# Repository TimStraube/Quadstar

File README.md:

# Thetafly

## Description

Thetafly is a project which includes python classes for simulating a quadcopter system. The simulation software is in a prototype stage with a lot of bugs still to be fixed and furture deep testing required.
With the help of the functionality a quadcopter prototyp has beeing build, mainly for fun and research purposes. The hardware is mostly finished but a lot of firmware still has to be written before flight testing can begin.

## Architecture

## Simulation

### Configuration

Make sure you setup a pyenv with the libs defined in pyproject.toml:

```pyenv activate thetafly```

Post activation of the pyenv you can simply run the simulator with a bash script:

```bash start.sh```

## Delopyment

### Joystick

To sample joystick values and send them to the main flight computer run:

```PYTHONPATH=src poetry run python -m util.joystick```.

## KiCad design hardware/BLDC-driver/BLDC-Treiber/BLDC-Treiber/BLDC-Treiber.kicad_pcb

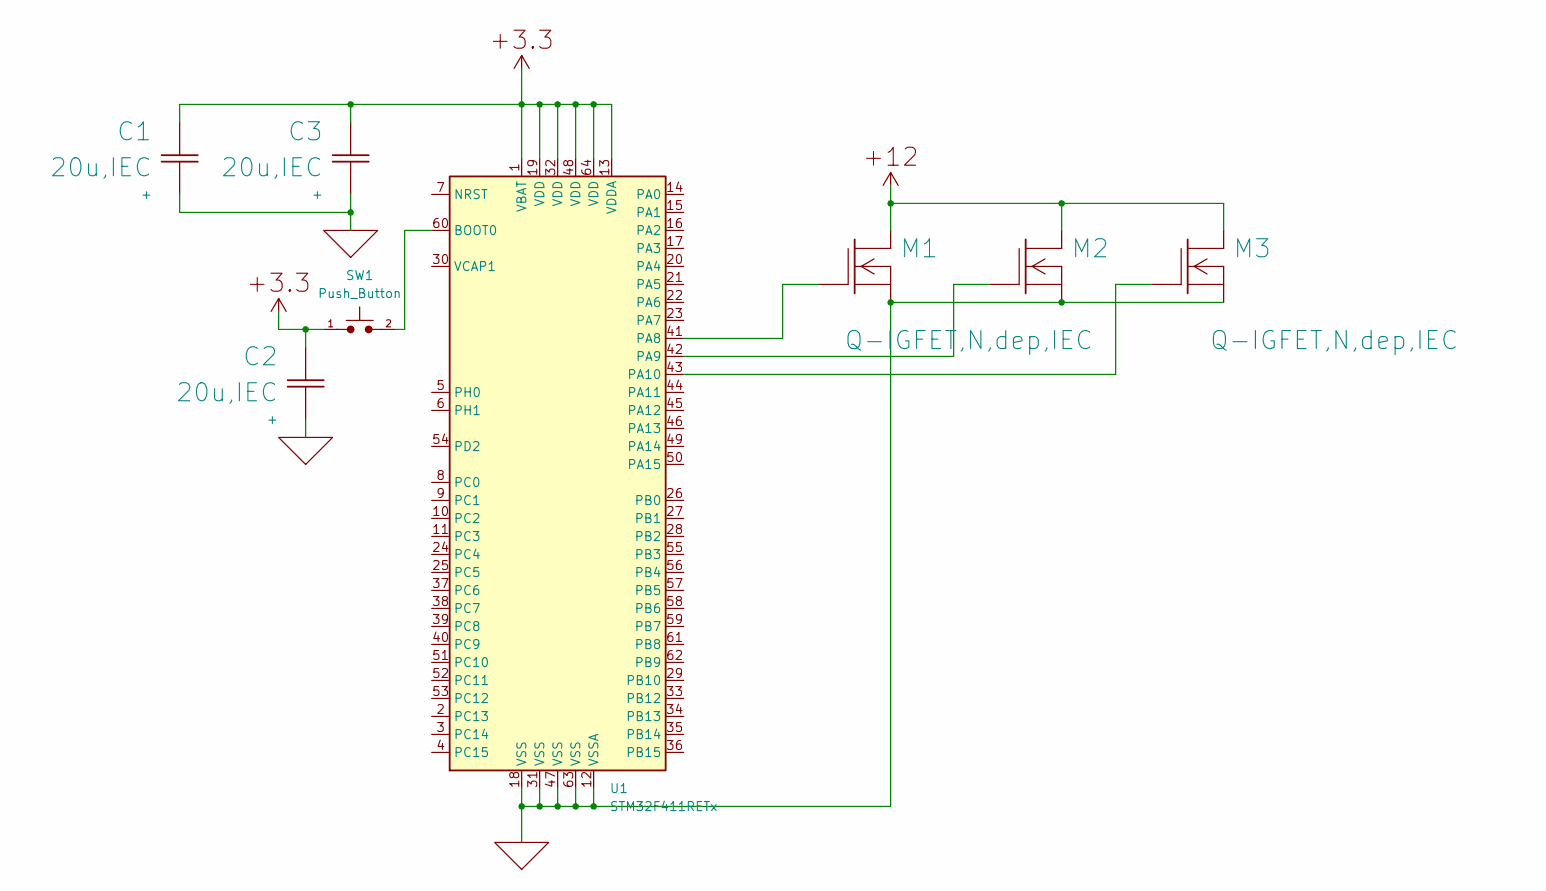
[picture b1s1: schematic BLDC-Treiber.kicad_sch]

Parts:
C1, C3: 20u,IEC; CP_Elec_8x5.4
C2: 20u,IEC; CP_Elec_3x5.3
M1, M2, M3: Q-IGFET,N,dep,IEC; DirectFET_SB
SW1: Push_Button; SW_PUSH_6mm
U1: STM32F411RETx; LQFP-64_10x10mm_P0.5mm

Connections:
unnamed: M1.2 (G), U1.41 (PA8)
unnamed: M2.2 (G), U1.42 (PA9)
unnamed: M3.2 (G), U1.43 (PA10)
unnamed: SW1.2, U1.60 (BOOT0)
P,+3.3: C1.1 (+), C2.1 (+), C3.1 (+), SW1.1, U1.1 (VBAT), U1.13 (VDDA), U1.19 (VDD), U1.32 (VDD), U1.48 (VDD), U1.64 (VDD)
P,+12: M1.1 (D), M2.1 (D), M3.1 (D)
P,GND: C1.2 (-), C2.2 (-), C3.2 (-), M1.3 (S), M2.3 (S), M3.3 (S), U1.12 (VSSA), U1.18 (VSS), U1.31 (VSS), U1.47 (VSS), U1.63 (VSS)

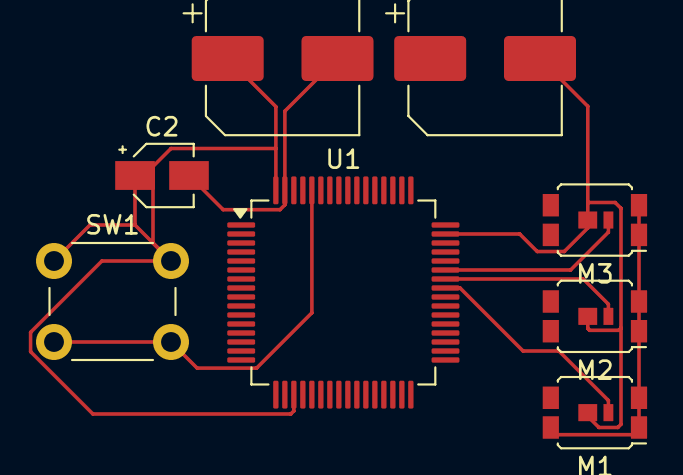
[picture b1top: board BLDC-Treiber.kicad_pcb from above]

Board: 2 copper layers, 8 parts (0 on the bottom side), 7 nets.

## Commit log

2024-09-27 Transfer from codeberg
2024-09-27 Remove unused images
2024-09-27 Cleanup
2024-09-27 Bug fixes
2024-09-27 Added quadsoft which includes the program for the onboard pid-controller
2024-09-28 Fixed bugs
2024-09-28 Changed language of README.md to english
2024-09-29 Updated LICENSE
2024-10-01 Started translation to english
2024-10-01 Translated variables and fixed bug in the report
2024-10-01 Added .gitignore
2024-10-01 Fixed images reference
2024-10-03 Removed temporary statements
2024-10-03 Bug fixes in the report
2024-10-04 Updated info and language
2024-10-05 Translated programs and fixed report
2024-10-06 Mores translations
2024-10-06 Fixed quadcopter dynamics model
2024-10-07 Small changes to quadsoft and translations
2024-10-07 Removed report and translations
2024-10-08 Automated config mechanism
2024-10-09 Removed models and translated
2024-10-09 Removed images
2024-10-09 Removed utils folder
2024-10-09 Translated quadsoft back to english
2024-10-13 Started KiCad modeling of driver
2024-10-13 Added link
2024-10-13 Test for the link
2024-10-13 Fixed link
2024-10-13 Added template_config
2024-10-15 Test
2024-10-15 Translation of quadsoft main.c
2024-10-22 Added program for flashing onto the mcu on the B-G431B-ESC1 bldc-motor controller
2024-10-25 Experiements with arm assembly for the quadesc
2024-10-28 Updates to README.md
2024-10-31 Fixed quadsoft main.c
2024-10-31 Fix for the fix
2024-10-31 Added timer period variable
2024-11-13 FM1 Testsoftware
2024-11-13 Removed test code
2024-11-21 Added program for testing ESCs
2024-11-22 Added TM1 program
2024-11-23 Added to README
2024-11-23 Added to README.md
2024-11-25 Fixed typo
2024-11-26 Started implementing a web based user interface
2024-11-26 Revert "Started implementing a web based user interface"
    This reverts commit b059f2e783513d7fa24e3bf69febb8f16645a011.
2024-11-29 Added ESC programm QM3
2024-11-29 Removed obsolet test programms
2024-11-29 Added motorctrl testprogram
2024-12-02 Removed quadserver
2024-12-11 Refactoring
2024-12-11 Added minimal requirements.txt
2025-02-13 New prototyp image
2025-02-13 Hopefully a fix
2025-05-13 feat: Corrected supply voltage
2025-05-14 chore: Moved python files
2025-07-25 feat: Initial commit for quadui
2025-07-25 feat: Update title and app name to QUADUI in index.html
2025-07-25 feat: Hinzufügen einer Geschwindigkeitsanzeige zur Home-Seite
2025-07-26 feat: Quadcom prototyp
2025-09-21 chore: Create v1.0.X
2025-09-21 feat: Hinzufügen von Testvorlagen für Motor ESC und Motor ESC Integration
2025-09-21 feat: Aktualisierung der Testvorlagen für Motor ESC und Motor ESC Integration mit neuen Erfolgsanforderungen
2025-09-21 feat: Aktualisierung der Erfolgsanforderungen und Hardwaredetails im Motor ESC Testdokument
2025-09-21 feat: Hinzufügen der Endzeit zum Motor ESC Testdokument
2025-09-21 feat: Implementierung der automatischen Zielgeschwindigkeitssteuerung im Motor ESC
2025-09-21 feat: Aktualisierung der Testdokumentation für Motor ESC mit neuen Eingangsparametern
2025-09-28 feat: Hinzufügen von Testdokumenten für Motor ESC mit spezifischen Ergebnissen und Hardwaredetails
2025-09-28 feat: Implementierung der automatischen Ramp-up Steuerung für Zielgeschwindigkeit im Motor ESC
2025-09-28 feat: Implementierung der PWM-Eingangssteuerung für die Zielgeschwindigkeit im Motor ESC
2025-09-28 feat: Hinzufügen eines Low-Pass-Filters für PWM-Eingang und Implementierung einer Ramp-up Steuerung für die Zielgeschwindigkeit
2025-09-29 feat: Hinzufügen von PWM-Initialisierung und Anpassung der Zielgeschwindigkeitskarte im ESC
2025-10-25 feat: Remote control prototyp
2025-10-25 feat: Thrust, pitch and roll communication
2025-10-27 test: Added tests and fixed README.md
2025-10-27 chore: Refactoring
2025-10-28 feat: Implementiere Controller- und InfoCard-Komponenten mit WebSocket-Integration für Motor- und Batteriedaten
2025-10-31 docs: Added to architecture diagram
2025-11-03 chore: Updated image
2025-11-03 fix: Path
2025-11-07 chore: Reorganized files and structure
2025-11-08 feat: Update
2025-11-08 feat: Updated architecture
2025-11-08 feat: Architecture diagram update
2025-11-08 chore: Update
2025-11-08 chore
2025-11-16 fix: Setup
2025-11-18 chore: Cleanup
2025-11-18 feat: Added MCU prototyp
2025-11-23 docs: Update
2025-11-29 feat: States and quadcom packets
2025-12-03 docs: Images for pinout
2025-12-03 feat: Prototype
2025-12-12 feat: UART test
2025-12-12 feat: Communication from esp32 to stm32
2025-12-12 feat: Added upload scripts
2025-12-13 feat: Reading IMU
2025-12-20 feat: Implemented thrust control via pwm from quadcom
2025-12-25 feat: Fixed cors
2025-12-25 feat: Cleanup
2025-12-26 feat: Add EnergyPanel component and integrate energy sampling in simulation
2025-12-30 fix: npm build
2025-12-30 fix: Update
